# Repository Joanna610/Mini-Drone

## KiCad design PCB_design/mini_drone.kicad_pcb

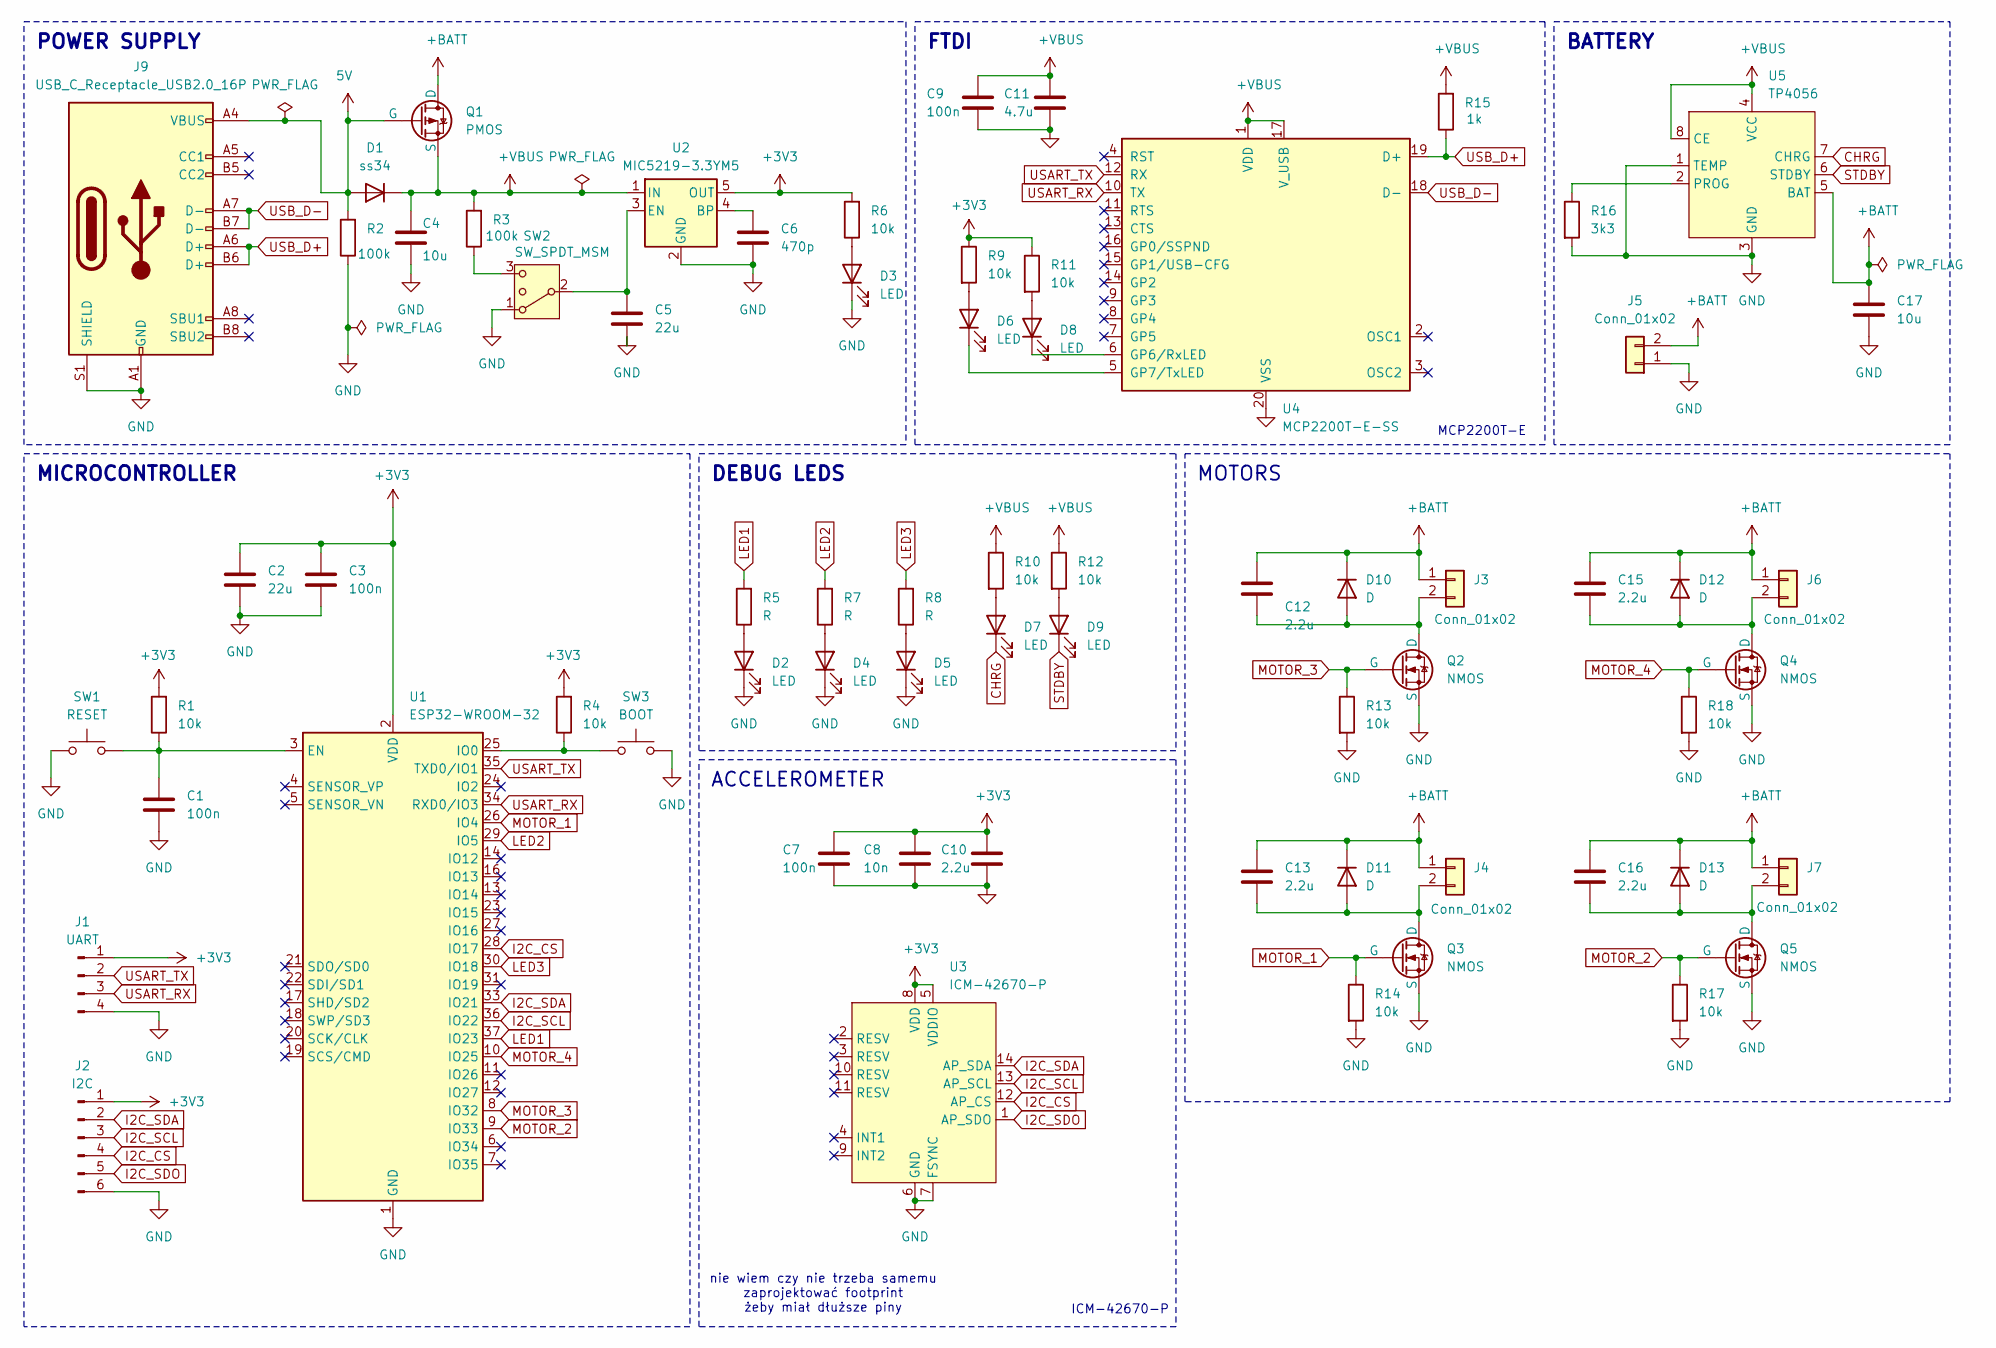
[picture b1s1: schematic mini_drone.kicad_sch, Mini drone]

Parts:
C1, C3, C7, C9: 100n; C_0603_1608Metric_Pad1.08x0.95mm_HandSolder
C2, C5: 22u; C_0603_1608Metric_Pad1.08x0.95mm_HandSolder
C4, C17: 10u; C_0603_1608Metric_Pad1.08x0.95mm_HandSolder
C6: 470p; C_0603_1608Metric_Pad1.08x0.95mm_HandSolder
C8: 10n; C_0603_1608Metric_Pad1.08x0.95mm_HandSolder
C10, C12, C13, C15, C16: 2.2u; C_0603_1608Metric_Pad1.08x0.95mm_HandSolder
C11: 4.7u; C_0603_1608Metric_Pad1.08x0.95mm_HandSolder
D1: ss34; D_SOD-128
D2, D3, D4, D5, D6, D7, D8, D9: LED; LED_0805_2012Metric_Pad1.15x1.40mm_HandSolder
D10, D11, D12, D13: D; D_SOD-128
J1: UART; PinHeader_1x04_P2.54mm_Vertical
J2: I2C; PinHeader_1x06_P2.54mm_Vertical
J3, J4, J5, J6, J7: Conn_01x02; Molex_SPOX_5267-02A_1x02_P2.50mm_Vertical
J9: USB_C_Receptacle_USB2.0_16P; USB_C_Receptacle_G-Switch_GT-USB-7010ASV
Q1: PMOS; SOT-23
Q2, Q3, Q4, Q5: NMOS; SOT-23
R1, R4, R6, R9, R10, R11, R12, R13, R14, R17, R18: 10k; R_0603_1608Metric_Pad0.98x0.95mm_HandSolder
R2, R3: 100k; R_0603_1608Metric_Pad0.98x0.95mm_HandSolder
R5, R7, R8: R; R_0603_1608Metric_Pad0.98x0.95mm_HandSolder
R15: 1k; R_0603_1608Metric_Pad0.98x0.95mm_HandSolder
R16: 3k3; R_0603_1608Metric_Pad0.98x0.95mm_HandSolder
SW1: RESET; SW_PUSH_1P1T_6x3.5mm_H4.3_APEM_MJTP1243
SW2: SW_SPDT_MSM; Nidec_Copal_CAS-120A
SW3: BOOT; SW_PUSH_1P1T_6x3.5mm_H4.3_APEM_MJTP1243
U1: ESP32-WROOM-32
U2: MIC5219-3.3YM5; SOT-23-5
U3: ICM-42670-P; LGA-14_3x2.5mm_P0.5mm_LayoutBorder3x4y
U4: MCP2200T-E-SS; SSOP-20_5.3x7.2mm_P0.65mm
U5: TP4056; SOP-8_3.76x4.96mm_P1.27mm

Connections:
5V: D1.2 (A), J9.A4 (VBUS), J9.A9 (VBUS), J9.B4 (VBUS), J9.B9 (VBUS), Q1.2 (G), R2.2
+3V3: C2.1, C3.1, C7.2, C8.2, C10.2, J1.1, J2.1, R1.2, R4.2, R6.2, R9.1, R11.1, U1.2 (VDD), U2.5 (OUT), U3.5 (VDDIO), U3.8 (VDD)
+BATT: C12.1, C13.1, C15.1, C16.1, C17.1, D10.1 (K), D11.1 (K), D12.1 (K), D13.1 (K), J3.1, J4.1, J5.2, J6.1, J7.1, Q1.1 (D), U5.5 (BAT)
+VBUS: C4.1, C9.2, C11.2, D1.1 (K), Q1.3 (S), R3.2, R10.1, R12.1, R15.2, U2.1 (IN), U4.1 (VDD), U4.17 (V_USB), U5.4 (VCC), U5.8 (CE)
CHRG: D7.1 (K), U5.7 (CHRG)
GND: C1.2, C2.2, C3.2, C4.2, C5.2, C6.2, C7.1, C8.1, C9.1, C10.1, C11.1, C17.2, D2.1 (K), D3.1 (K), D4.1 (K), D5.1 (K), J1.4, J2.6, J5.1, J9.A1 (GND), J9.A12 (GND), J9.B1 (GND), J9.B12 (GND), J9.S1 (SHIELD), Q2.3 (S), Q3.3 (S), Q4.3 (S), Q5.3 (S), R2.1, R13.2, R14.2, R16.2, R17.2, R18.2, SW1.1, SW2.1, SW3.2, U1.1 (GND), U1.15 (GND), U1.38 (GND), U1.39 (GND), U2.2 (GND), U3.6 (GND), U3.7 (FSYNC), U4.20 (VSS), U5.1 (TEMP), U5.3 (GND)
I2C_CS: J2.4, U1.28 (IO17), U3.12 (AP_CS)
I2C_SCL: J2.3, U1.36 (IO22), U3.13 (AP_SCL)
I2C_SDA: J2.2, U1.33 (IO21), U3.14 (AP_SDA)
I2C_SDO: J2.5, U3.1 (AP_SDO)
LED1: R5.2, U1.37 (IO23)
LED2: R7.2, U1.29 (IO5)
LED3: R8.2, U1.30 (IO18)
MOTOR_1: Q3.2 (G), R14.1, U1.26 (IO4)
MOTOR_2: Q5.2 (G), R17.1, U1.9 (IO33)
MOTOR_3: Q2.2 (G), R13.1, U1.8 (IO32)
MOTOR_4: Q4.2 (G), R18.1, U1.10 (IO25)
unnamed: D2.2 (A), R5.1
unnamed: D3.2 (A), R6.1
unnamed: D4.2 (A), R7.1
unnamed: D5.2 (A), R8.1
unnamed: D6.2 (A), R9.2
unnamed: D6.1 (K), U4.5 (GP7/TxLED)
unnamed: D7.2 (A), R10.2
unnamed: D8.2 (A), R11.2
unnamed: D8.1 (K), U4.6 (GP6/RxLED)
unnamed: D9.2 (A), R12.2
unnamed: C12.2, D10.2 (A), J3.2, Q2.1 (D)
unnamed: C13.2, D11.2 (A), J4.2, Q3.1 (D)
unnamed: C15.2, D12.2 (A), J6.2, Q4.1 (D)
unnamed: C16.2, D13.2 (A), J7.2, Q5.1 (D)
unnamed: C5.1, SW2.2 (3), U2.3 (EN)
unnamed: R3.1, SW2.3 (4)
unnamed: C1.1, R1.1, SW1.2, U1.3 (EN)
unnamed: R4.1, SW3.1, U1.25 (IO0)
unnamed: C6.1, U2.4 (BP)
unnamed: R16.1, U5.2 (PROG)
STDBY: D9.1 (K), U5.6 (STDBY)
USART_RX: J1.3, U1.34 (RXD0/IO3), U4.10 (TX)
USART_TX: J1.2, U1.35 (TXD0/IO1), U4.12 (RX)
USB_D+: J9.A6 (D+), J9.B6 (D+), R15.1, U4.19 (D+)
USB_D-: J9.A7 (D-), J9.B7 (D-), U4.18 (D-)

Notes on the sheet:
DEBUG LEDS
FTDI
ACCELEROMETER
MICROCONTROLLER
BATTERY
POWER SUPPLY
MOTORS
nie wiem czy nie trzeba samemu zaprojektować footprint żeby miał dłuższe piny
ICM-42670-P
MCP2200T-E

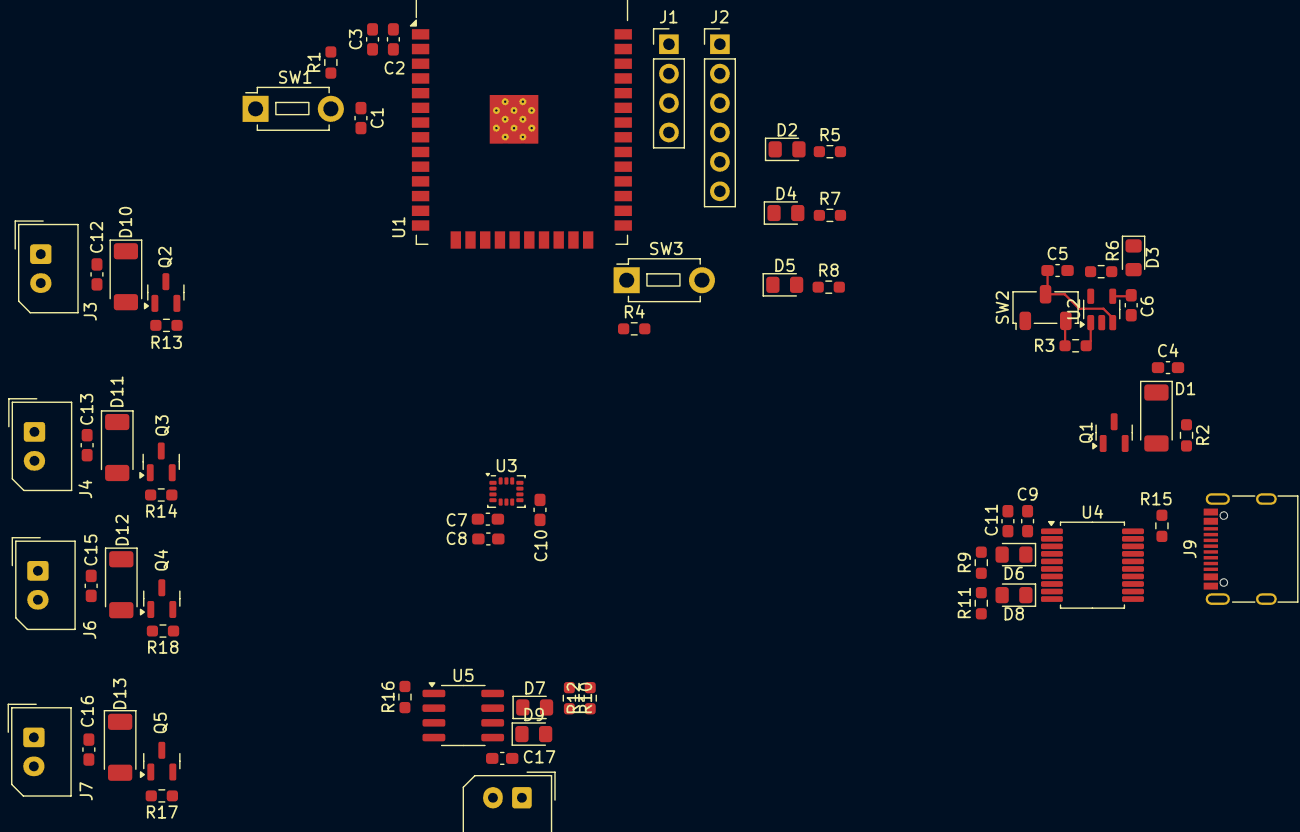
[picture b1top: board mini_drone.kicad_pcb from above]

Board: 2 copper layers, 68 parts (0 on the bottom side), 42 nets.
